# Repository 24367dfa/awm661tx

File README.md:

awm661tx
========

First prototype for a 5g8 video transmitter based on the airwave awm661tx module.
No prototype yet, just planning.

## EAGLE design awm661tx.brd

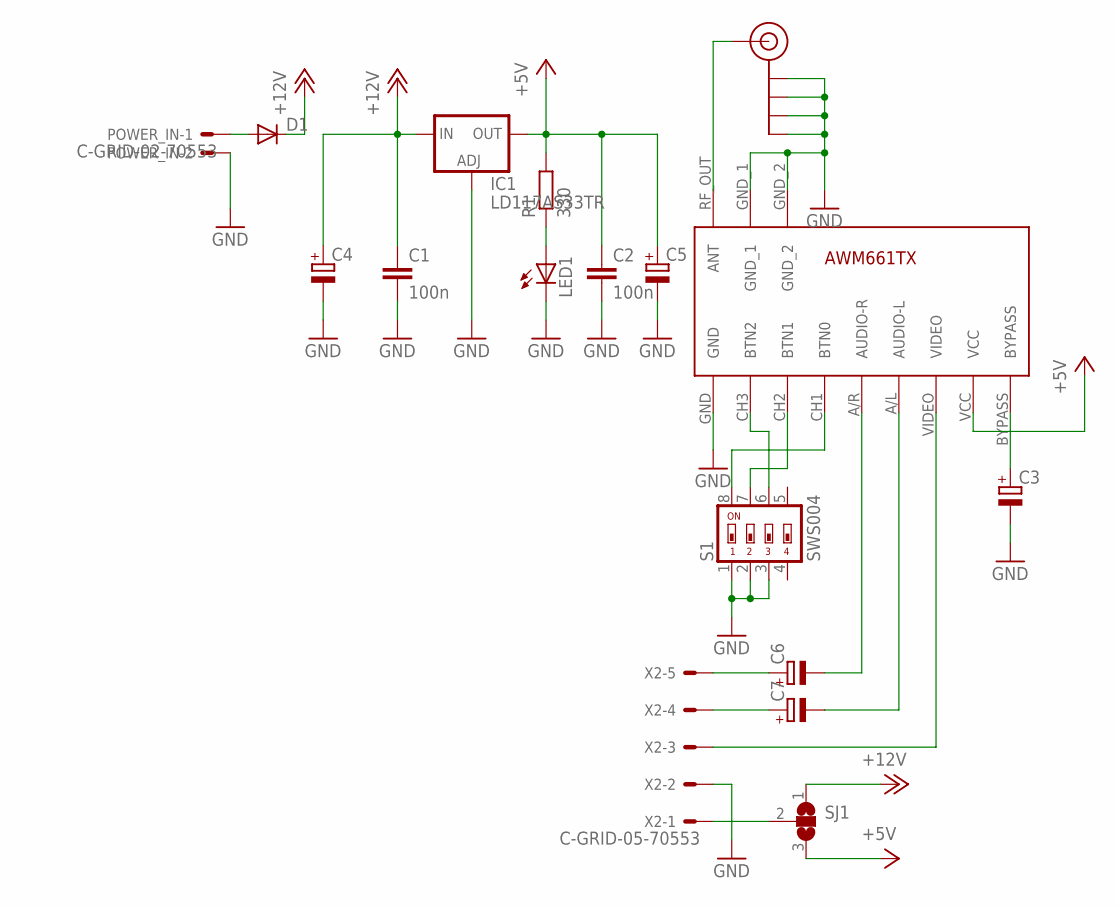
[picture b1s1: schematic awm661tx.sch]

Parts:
C1, C2: 100n; C0805
C3, C4, C5: CPOL-EU150CLZ-0810; 150CLZ-0810
C6, C7: CPOL-EU153CLV-0505; 153CLV-0505
D1: DIODE-MELF-MLL41; MELF-MLL41
IC1: LD117AS33TR; SOT223
J$1: SMA_EDGE; SMA-EDGE
LED1: LEDCHIP-LED0805; CHIP-LED0805
POWER_IN: C-GRID-02-70553; 70553-02
R1: 330; R0805
S1: SWS004; SMS-004
SJ1: SJ2W; SJ_2
U$1: AWM661TX
X2: C-GRID-05-70553; 70553-05

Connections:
+5V: C2.1, C5.+, IC1.4 (OUT), R1.2, SJ1.3, U$1.VCC
+12V: C1.1, C4.+, D1.C, IC1.3 (IN), SJ1.1
GND: C1.2, C2.2, C3.-, C4.-, C5.-, IC1.1 (ADJ), J$1.GND@0 (GND), J$1.GND@1 (GND), J$1.GND@2 (GND), J$1.GND@3 (GND), LED1.C, POWER_IN.2, S1.1, S1.2, S1.3, U$1.GND, U$1.GND_1, U$1.GND_2, X2.2
unnamed: D1.A, POWER_IN.1
unnamed: LED1.A, R1.1
unnamed: J$1.SIG (SIGNAL), U$1.RF_OUT (ANT)
unnamed: S1.7, U$1.CH2 (BTN1)
unnamed: S1.6, U$1.CH3 (BTN2)
unnamed: S1.8, U$1.CH1 (BTN0)
unnamed: C6.+, X2.5
unnamed: C6.-, U$1.A/R (AUDIO-R)
unnamed: C7.-, U$1.A/L (AUDIO-L)
unnamed: C7.+, X2.4
unnamed: U$1.VIDEO, X2.3
unnamed: C3.+, U$1.BYPASS
unnamed: SJ1.2, X2.1

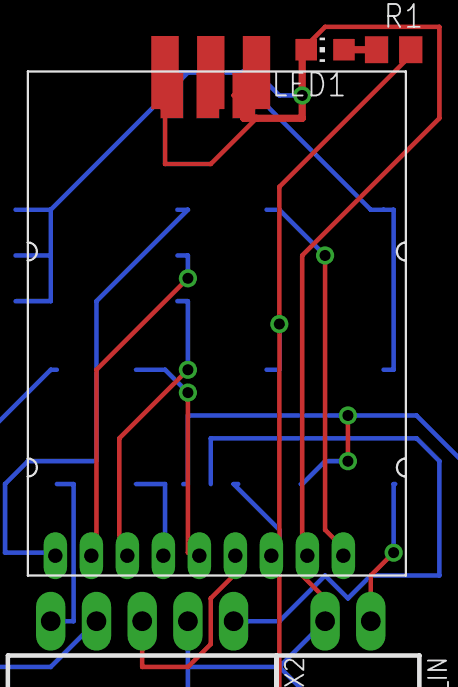
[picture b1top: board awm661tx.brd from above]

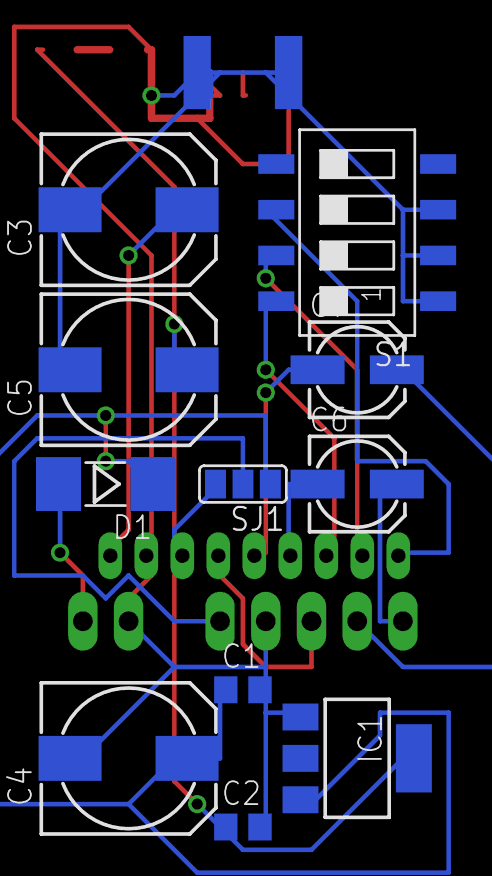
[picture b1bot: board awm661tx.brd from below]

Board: 2 copper layers, 17 parts (11 on the bottom side), 16 nets.

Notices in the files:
parts and their libraries:
SparkFun-Connectors: Licensing: CC v3.0 Share-Alike You are welcome to use this library for commercial purposes.
